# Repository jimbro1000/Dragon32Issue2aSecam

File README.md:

# Dragon 32 Issue 2a (SECAM) Reproduction

This repository contains the KiCad project files
to reproduce the SECAM variation of the Dragon 32
Issue 2a main board.

This design requires the SECAM power board to operate
correctly and will not work with the standard board.
See https://github.com/jimbro1000/Dragon32PowerSecam

## Notes

The board incorporates some factory bodges to simplify
assembly efforts.

A front and back ground plane fill has also been added
along with effort to make sure that a ground plane is 
present across most of the board.

## Video Circuit Changes

Compared to the original Dragon 32 (in PAL or NTSC form)
the SECAM version of the design requires a significant 
level of additional work to generate a viable composite
signal.

The most significant change is that the board does not 
make use of a modulator chip (the LM1889N is used on
the PAL version). Instead the generation of the FM based
composite signal is generated through discrete components.

The board is effectively split into two areas. The regular
PAL design (with a few small tweaks) and the SECAM composite
generation - located in the north section of the PCB.

## Power Board Changes

While the same 9 wire interconnect is present on both
designs, the SECAM version repurposes the 5 non-voltage
connections making the power board incompatible with the
PAL/NTSC main board and the SECAM main board incompatible
with the PAL/NTSC power board.

The original pin out provided ground, composite, audio, 5v
and a bias voltage.

The SECAM board uses the same pins as audio, composite,
luma, phiA and phiB (the last 3 forming a YPrPb signal). 
By passing the raw output of the VDG to the power board
there is space to perform additional transformation into
a genuine RGB output that is sorely missing from the original.

### RGB Calculation

The transformation is performed in two stages - first to
homogenise the signal levels of the VDG output (while it 
broadly follows the YPrPb format it doesn't meet the requried
signal voltages). The second stage performs some analogue
computation to create R-Y, G-Y and B-Y components. These
then can be added to the homogenised Y signal to create
the three R, G and B signals.

An exta calculation is needed to isolate the sync signal
that appears on the G channel.

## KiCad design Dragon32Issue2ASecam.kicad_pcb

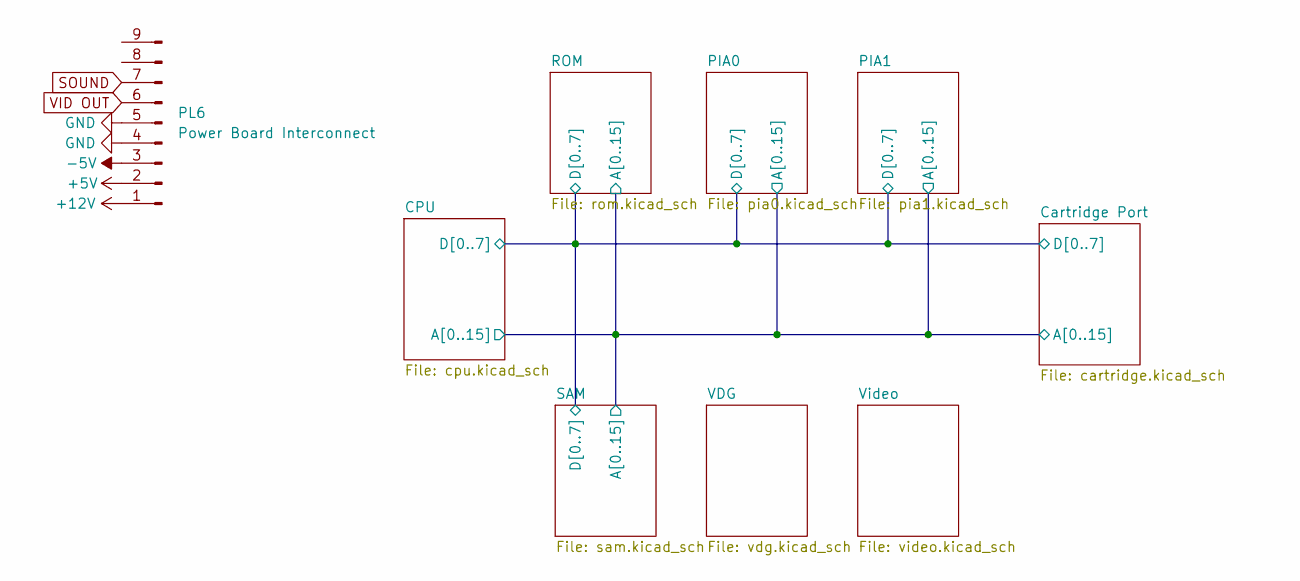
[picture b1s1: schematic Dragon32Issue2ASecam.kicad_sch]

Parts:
PL6: Power Board Interconnect; Molex_KK-396_A-41791-0009_1x09_P3.96mm_Vertical; DigiKey 2057-LHD-09-TS-ND

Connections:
+5V: PL6.2; also elsewhere on the board
+12V: PL6.1; also elsewhere on the board
-5V: PL6.3
GND: PL6.4, PL6.5; also elsewhere on the board
SOUND: PL6.7; also elsewhere on the board
VID OUT: PL6.6

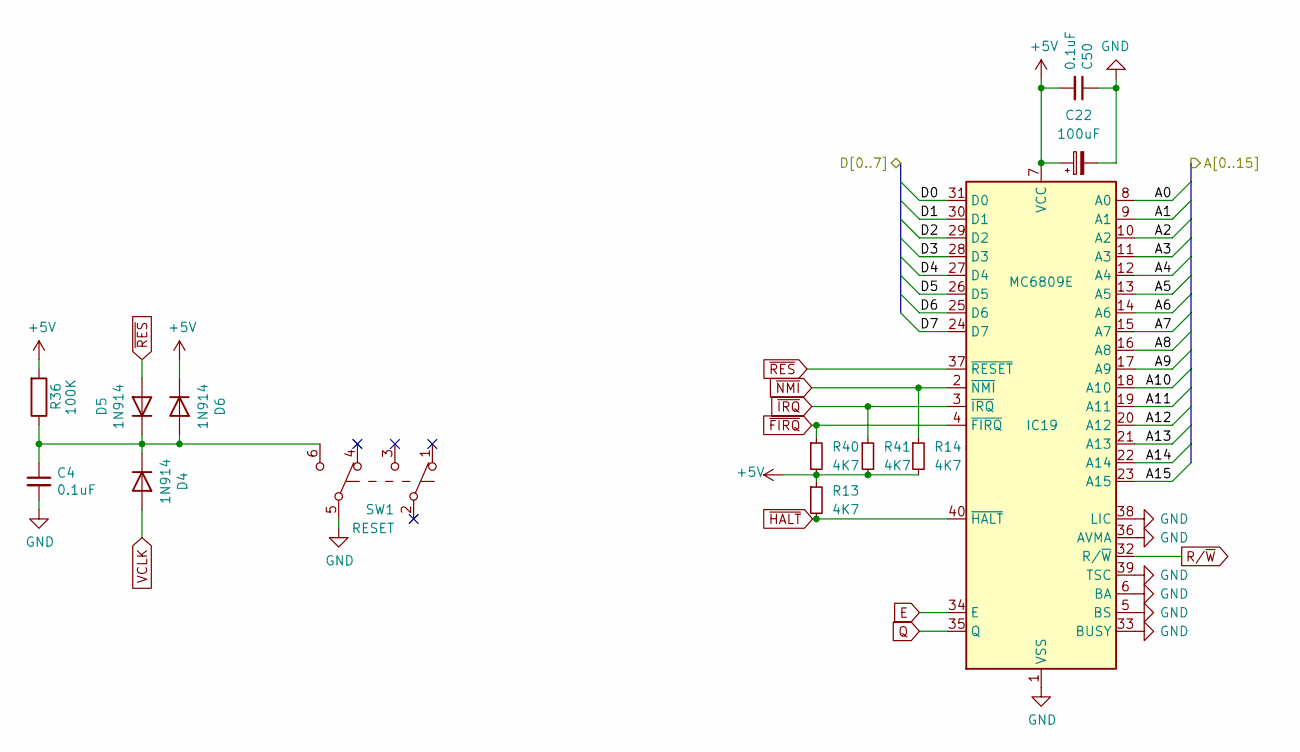
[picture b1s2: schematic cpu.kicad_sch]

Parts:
C4, C50: 0.1uF; C_Disc_D4.3mm_W1.9mm_P5.00mm; DigiKey BC1101CT-ND
C22: 100uF; CP_Radial_D8.0mm_P5.00mm; DigiKey 732-8598-1-ND
D4, D5, D6: 1N914; D_DO-35_SOD27_P12.70mm_Horizontal; DigiKey 1N914FS-ND
IC19: MC6809E; DIP-40_W15.24mm
R13, R14, R40, R41: 4K7; R_Axial_DIN0309_L9.0mm_D2.5mm_P12.70mm_Horizontal; DigiKey CF14JT4K70CT-ND
R36: 100K; R_Axial_DIN0309_L9.0mm_D2.5mm_P12.70mm_Horizontal; DigiKey CF14JT100KCT-ND
SW1: RESET; Button_AlpsAlpine_SPUN190900; DigiKey 401-1225-ND

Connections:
+5V: C22.1, C50.2, D6.1 (K), IC19.7 (VCC), R13.1, R14.2, R36.2, R40.2, R41.2; also elsewhere on the board
/CPU/A0: IC19.8 (A0); also elsewhere on the board
/CPU/A1: IC19.9 (A1); also elsewhere on the board
/CPU/A2: IC19.10 (A2); also elsewhere on the board
/CPU/A3: IC19.11 (A3); also elsewhere on the board
/CPU/A4: IC19.12 (A4); also elsewhere on the board
/CPU/A5: IC19.13 (A5); also elsewhere on the board
/CPU/A6: IC19.14 (A6); also elsewhere on the board
/CPU/A7: IC19.15 (A7); also elsewhere on the board
/CPU/A8: IC19.16 (A8); also elsewhere on the board
/CPU/A9: IC19.17 (A9); also elsewhere on the board
/CPU/A10: IC19.18 (A10); also elsewhere on the board
/CPU/A11: IC19.19 (A11); also elsewhere on the board
/CPU/A12: IC19.20 (A12); also elsewhere on the board
/CPU/A13: IC19.21 (A13); also elsewhere on the board
/CPU/A14: IC19.22 (A14); also elsewhere on the board
/CPU/A15: IC19.23 (A15); also elsewhere on the board
/CPU/D0: IC19.31 (D0); also elsewhere on the board
/CPU/D1: IC19.30 (D1); also elsewhere on the board
/CPU/D2: IC19.29 (D2); also elsewhere on the board
/CPU/D3: IC19.28 (D3); also elsewhere on the board
/CPU/D4: IC19.27 (D4); also elsewhere on the board
/CPU/D5: IC19.26 (D5); also elsewhere on the board
/CPU/D6: IC19.25 (D6); also elsewhere on the board
/CPU/D7: IC19.24 (D7); also elsewhere on the board
E: IC19.34 (E); also elsewhere on the board
GND: C4.2, C22.2, C50.1, IC19.1 (VSS), IC19.5 (BS), IC19.6 (BA), IC19.33 (BUSY), IC19.36 (AVMA), IC19.38 (LIC), IC19.39 (TSC), SW1.5 (B); also elsewhere on the board
unnamed: C4.1, D4.1 (K), D5.1 (K), D6.2 (A), R36.1, SW1.6 (C)
Q: IC19.35 (Q); also elsewhere on the board
R/~W: IC19.32 (R/~W); also elsewhere on the board
VCLK: D4.2 (A); also elsewhere on the board
~FIRQ: IC19.4 (~FIRQ), R40.1; also elsewhere on the board
~HALT: IC19.40 (~HALT), R13.2; also elsewhere on the board
~IRQ: IC19.3 (~IRQ), R41.1; also elsewhere on the board
~NMI: IC19.2 (~NMI), R14.1; also elsewhere on the board
~RES: D5.2 (A), IC19.37 (~RESET); also elsewhere on the board

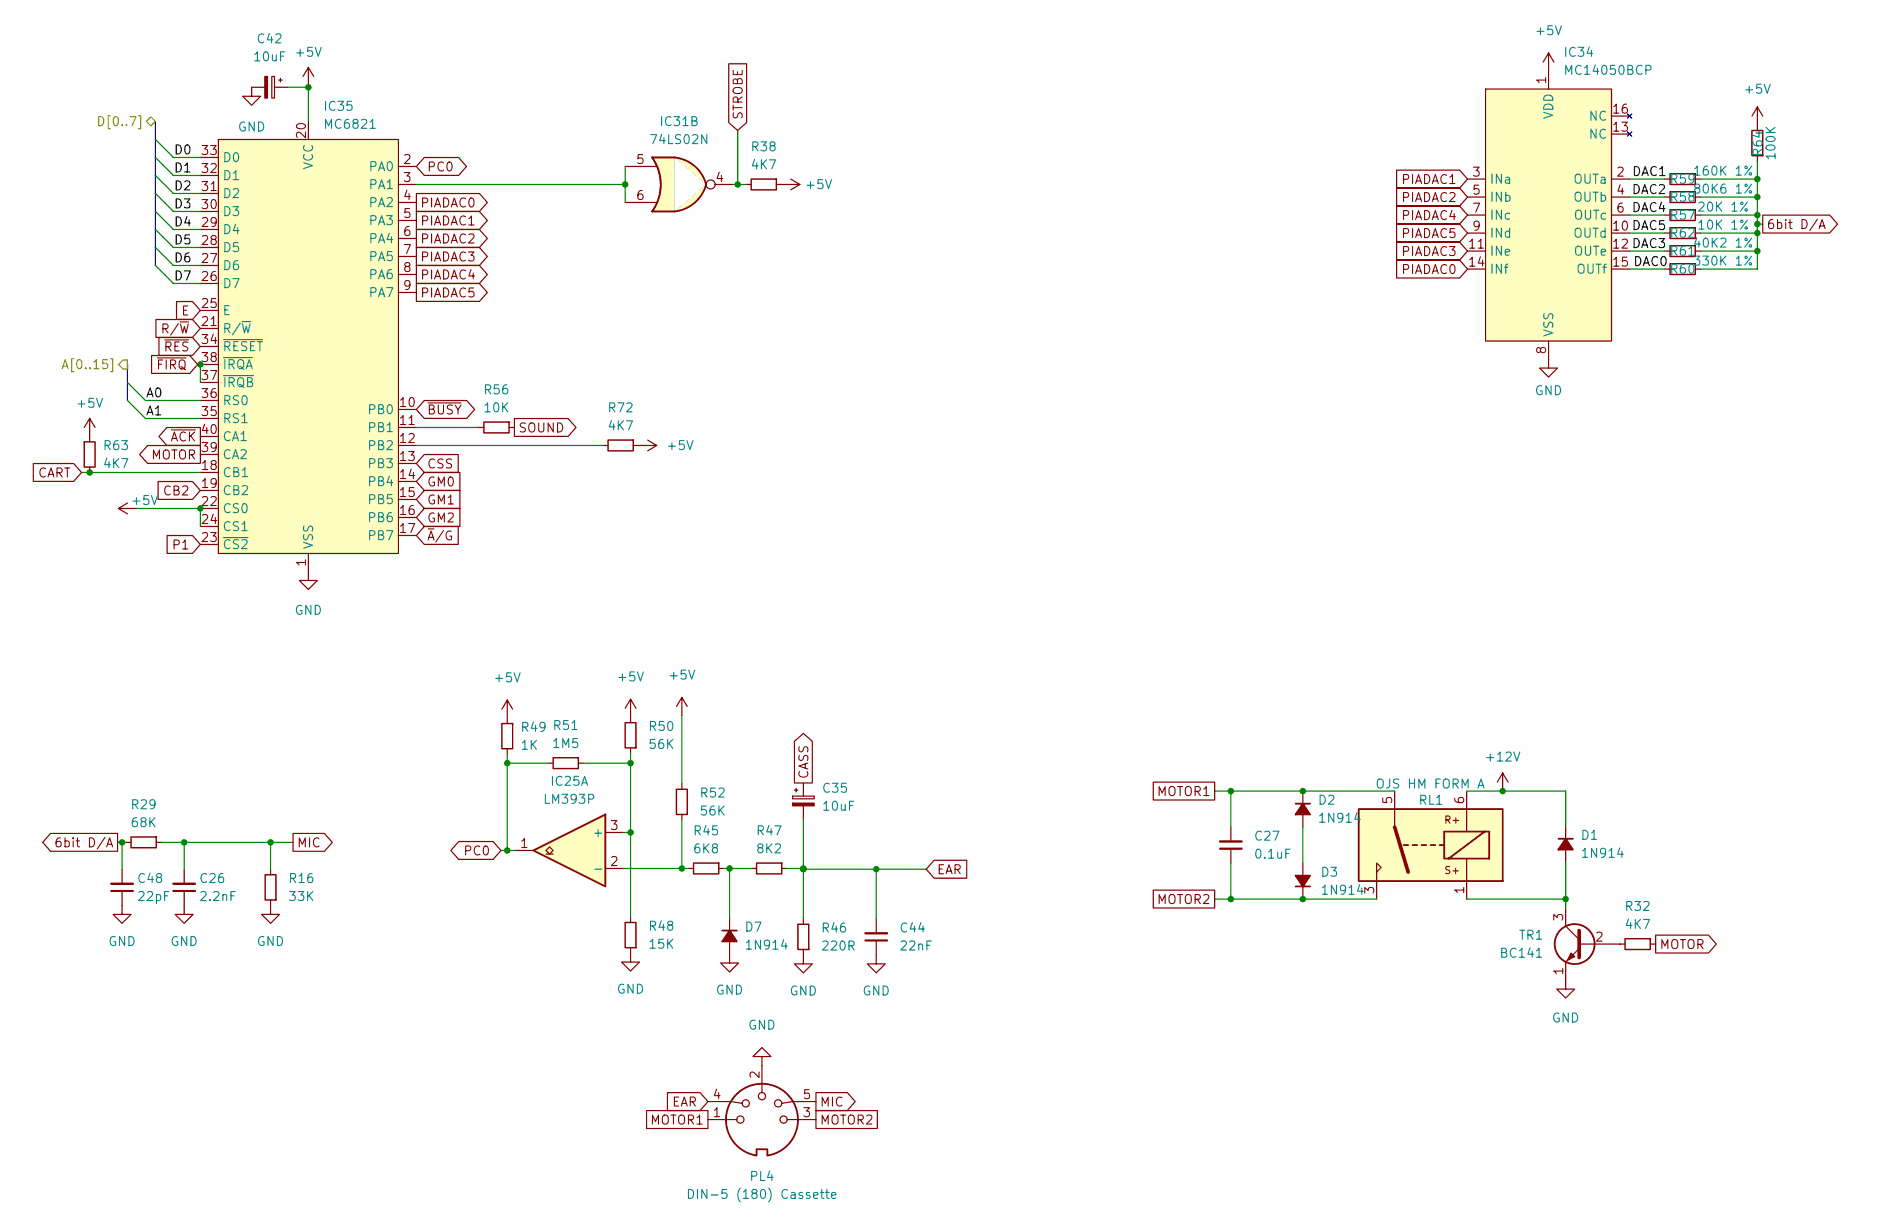
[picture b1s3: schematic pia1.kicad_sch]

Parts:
C26: 2.2nF; C_Disc_D4.3mm_W1.9mm_P5.00mm; DigiKey BC1074CT-ND
C27: 0.1uF; C_Disc_D4.3mm_W1.9mm_P5.00mm; DigiKey BC1101CT-ND
C35, C42: 10uF; CP_Radial_D5.0mm_P2.50mm; DigiKey 732-8593-1-ND
C44: 22nF; C_Disc_D5.0mm_W2.5mm_P5.00mm; DigiKey BC2677CT-ND
C48: 22pF; C_Disc_D3.0mm_W2.0mm_P2.50mm; DigiKey 399-13930-1-ND
D1, D2, D3, D7: 1N914; D_DO-35_SOD27_P12.70mm_Horizontal; DigiKey 1N914FS-ND
IC25: LM393P; DIP-8_W7.62mm; DigiKey 296-1398-5-ND
IC31: 74LS02N; DIP-14_W7.62mm; DigiKey 296-1627-5-ND
IC34: MC14050BCP; DIP-16_W7.62mm; DigiKey 296-2056-ND
IC35: MC6821; DIP-40_W15.24mm; DigiKey 2156-MC6821CS-2156-ND
PL4: DIN-5 (180) Cassette; DIN-5_DELTRON_671-0501_45deg_Horizontal
R16: 33K; R_Axial_DIN0309_L9.0mm_D2.5mm_P12.70mm_Horizontal; DigiKey CF14JT33K0CT-ND
R29: 68K; R_Axial_DIN0309_L9.0mm_D2.5mm_P12.70mm_Horizontal; DigiKey CF14JT68K0CT-ND
R32, R38, R63: 4K7; R_Axial_DIN0309_L9.0mm_D2.5mm_P12.70mm_Horizontal; DigiKey CF14JT4K70CT-ND
R45: 6K8; R_Axial_DIN0309_L9.0mm_D2.5mm_P12.70mm_Horizontal; DigiKey CF14JT6K80CT-ND
R46: 220R; R_Axial_DIN0309_L9.0mm_D2.5mm_P12.70mm_Horizontal; DigiKey CF14JT220RCT-ND
R47: 8K2; R_Axial_DIN0309_L9.0mm_D2.5mm_P12.70mm_Horizontal; DigiKey CF14JT8K20CT-ND
R48: 15K; R_Axial_DIN0309_L9.0mm_D2.5mm_P12.70mm_Horizontal; DigiKey CF14JT15K0CT-ND
R49: 1K; R_Axial_DIN0309_L9.0mm_D2.5mm_P12.70mm_Horizontal; DigiKey CF14JT1K00CT-ND
R50, R52: 56K; R_Axial_DIN0309_L9.0mm_D2.5mm_P12.70mm_Horizontal; DigiKey CF14JT56K0CT-ND
R51: 1M5; R_Axial_DIN0309_L9.0mm_D2.5mm_P12.70mm_Horizontal; DigiKey CF14JT1M50CT-ND
R56: 10K; R_Axial_DIN0309_L9.0mm_D2.5mm_P12.70mm_Horizontal; DigiKey CF14JT10K0CT-ND
R57: 20K 1%; R_Axial_DIN0309_L9.0mm_D2.5mm_P12.70mm_Horizontal; DigiKey RNF14FTD20K0CT-ND
R58: 80K6 1%; R_Axial_DIN0309_L9.0mm_D2.5mm_P12.70mm_Horizontal; DigiKey RNF14FTD80K6CT-ND
R59: 160K 1%; R_Axial_DIN0309_L9.0mm_D2.5mm_P12.70mm_Horizontal; DigiKey S160CACT-ND
R60: 330K 1%; R_Axial_DIN0309_L9.0mm_D2.5mm_P12.70mm_Horizontal; DigiKey S330KCACT-ND
R61: 40K2 1%; R_Axial_DIN0309_L9.0mm_D2.5mm_P12.70mm_Horizontal; DigiKey RNF14FTD41K2CT-ND
R62: 10K 1%; R_Axial_DIN0309_L9.0mm_D2.5mm_P12.70mm_Horizontal; DigiKey RNF14FTD10K0CT-ND
R64: 100K; R_Axial_DIN0309_L9.0mm_D2.5mm_P12.70mm_Horizontal; DigiKey CF14JT100KCT-ND
R72: 4K7; R_Axial_DIN0309_L9.0mm_D2.5mm_P12.70mm_Horizontal; DigiKey CF14JT10K0CT-ND
RL1: OJS HM FORM A; OJS HM 10A Relay; DigiKey 41-OJS-SH-105HMF,00000-ND
TR1: BC141; TO-92_Inline_Wide; DigiKey SS8050DTACT-ND

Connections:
6bit D/A: C48.2, R29.2, R57.1, R58.1, R59.1, R60.1, R61.1, R62.1, R64.1; also elsewhere on the board
+5V: C42.1, IC34.1 (VDD), IC35.20 (VCC), IC35.22 (CS0), IC35.24 (CS1), R38.1, R49.1, R50.2, R52.2, R63.1, R64.2, R72.1; also elsewhere on the board
+12V: D1.1 (K), RL1.6; also elsewhere on the board
/CPU/A0: IC35.36 (RS0); also elsewhere on the board
/CPU/A1: IC35.35 (RS1); also elsewhere on the board
/CPU/D0: IC35.33 (D0); also elsewhere on the board
/CPU/D1: IC35.32 (D1); also elsewhere on the board
/CPU/D2: IC35.31 (D2); also elsewhere on the board
/CPU/D3: IC35.30 (D3); also elsewhere on the board
/CPU/D4: IC35.29 (D4); also elsewhere on the board
/CPU/D5: IC35.28 (D5); also elsewhere on the board
/CPU/D6: IC35.27 (D6); also elsewhere on the board
/CPU/D7: IC35.26 (D7); also elsewhere on the board
/PIA1/DAC0: IC34.15 (OUTf), R60.2
/PIA1/DAC1: IC34.2 (OUTa), R59.2
/PIA1/DAC2: IC34.4 (OUTb), R58.2
/PIA1/DAC3: IC34.12 (OUTe), R61.2
/PIA1/DAC4: IC34.6 (OUTc), R57.2
/PIA1/DAC5: IC34.10 (OUTd), R62.2
CART: IC35.18 (CB1), R63.2; also elsewhere on the board
CASS: C35.1; also elsewhere on the board
CB2: IC35.19 (CB2); also elsewhere on the board
CSS: IC35.13 (PB3); also elsewhere on the board
E: IC35.25 (E); also elsewhere on the board
EAR: C35.2, C44.2, PL4.4, R46.2, R47.1
GM0: IC35.14 (PB4); also elsewhere on the board
GM1: IC35.15 (PB5); also elsewhere on the board
GM2: IC35.16 (PB6); also elsewhere on the board
GND: C26.1, C42.2, C44.1, C48.1, D7.2 (A), IC34.8 (VSS), IC35.1 (VSS), PL4.2, R16.1, R46.1, R48.1, TR1.1 (E); also elsewhere on the board
MIC: C26.2, PL4.5, R16.2, R29.1
MOTOR: IC35.39 (CA2), R32.1
MOTOR1: C27.2, D2.1 (K), PL4.1, RL1.5
MOTOR2: C27.1, D3.1 (K), PL4.3, RL1.3
unnamed: D1.2 (A), RL1.1, TR1.3 (C)
unnamed: D2.2 (A), D3.2 (A)
unnamed: D7.1 (K), R45.1, R47.2
unnamed: IC25.3 (+), R48.2, R50.1, R51.1
unnamed: IC25.2 (-), R45.2, R52.1
unnamed: IC31.5, IC31.6, IC35.3 (PA1)
unnamed: IC35.11 (PB1), R56.2
unnamed: IC35.12 (PB2), R72.2
unnamed: R32.2, TR1.2 (B)
P1: IC35.23 (~CS2); also elsewhere on the board
PC0: IC25.1, IC35.2 (PA0), R49.2, R51.2
PIADAC0: IC34.14 (INf), IC35.4 (PA2)
PIADAC1: IC34.3 (INa), IC35.5 (PA3)
PIADAC2: IC34.5 (INb), IC35.6 (PA4)
PIADAC3: IC34.11 (INe), IC35.7 (PA5)
PIADAC4: IC34.7 (INc), IC35.8 (PA6)
PIADAC5: IC34.9 (INd), IC35.9 (PA7)
R/~W: IC35.21 (R/~W); also elsewhere on the board
SOUND: R56.1; also elsewhere on the board
STROBE: IC31.4, R38.2; also elsewhere on the board
~ACK: IC35.40 (CA1); also elsewhere on the board
~A/G: IC35.17 (PB7); also elsewhere on the board
~BUSY: IC35.10 (PB0); also elsewhere on the board
~FIRQ: IC35.37 (~IRQB), IC35.38 (~IRQA); also elsewhere on the board
~RES: IC35.34 (~RESET); also elsewhere on the board

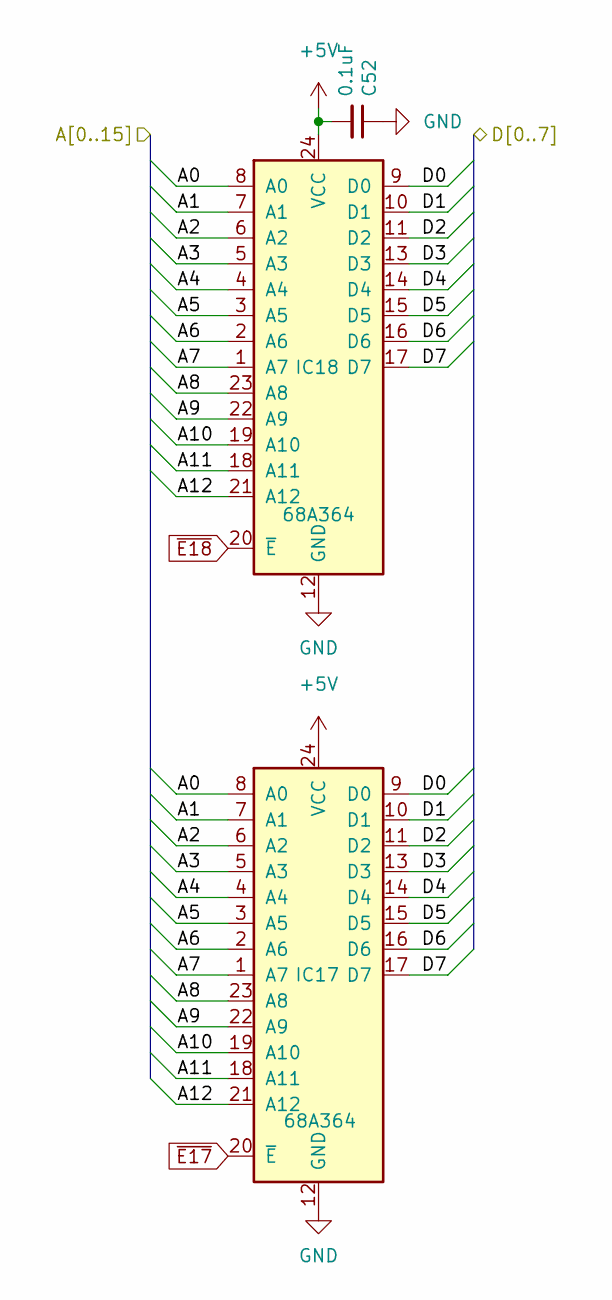
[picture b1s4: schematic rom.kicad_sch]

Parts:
C52: 0.1uF; C_Disc_D4.3mm_W1.9mm_P5.00mm; DigiKey BC1101CT-ND
IC17, IC18: 68A364; DIP-24_W15.24mm

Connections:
+5V: C52.2, IC17.24 (VCC), IC18.24 (VCC); also elsewhere on the board
/CPU/A0: IC17.8 (A0), IC18.8 (A0); also elsewhere on the board
/CPU/A1: IC17.7 (A1), IC18.7 (A1); also elsewhere on the board
/CPU/A2: IC17.6 (A2), IC18.6 (A2); also elsewhere on the board
/CPU/A3: IC17.5 (A3), IC18.5 (A3); also elsewhere on the board
/CPU/A4: IC17.4 (A4), IC18.4 (A4); also elsewhere on the board
/CPU/A5: IC17.3 (A5), IC18.3 (A5); also elsewhere on the board
/CPU/A6: IC17.2 (A6), IC18.2 (A6); also elsewhere on the board
/CPU/A7: IC17.1 (A7), IC18.1 (A7); also elsewhere on the board
/CPU/A8: IC17.23 (A8), IC18.23 (A8); also elsewhere on the board
/CPU/A9: IC17.22 (A9), IC18.22 (A9); also elsewhere on the board
/CPU/A10: IC17.19 (A10), IC18.19 (A10); also elsewhere on the board
/CPU/A11: IC17.18 (A11), IC18.18 (A11); also elsewhere on the board
/CPU/A12: IC17.21 (A12), IC18.21 (A12); also elsewhere on the board
/CPU/D0: IC17.9 (D0), IC18.9 (D0); also elsewhere on the board
/CPU/D1: IC17.10 (D1), IC18.10 (D1); also elsewhere on the board
/CPU/D2: IC17.11 (D2), IC18.11 (D2); also elsewhere on the board
/CPU/D3: IC17.13 (D3), IC18.13 (D3); also elsewhere on the board
/CPU/D4: IC17.14 (D4), IC18.14 (D4); also elsewhere on the board
/CPU/D5: IC17.15 (D5), IC18.15 (D5); also elsewhere on the board
/CPU/D6: IC17.16 (D6), IC18.16 (D6); also elsewhere on the board
/CPU/D7: IC17.17 (D7), IC18.17 (D7); also elsewhere on the board
GND: C52.1, IC17.12 (GND), IC18.12 (GND); also elsewhere on the board
~E17: IC17.20 (~E); also elsewhere on the board
~E18: IC18.20 (~E); also elsewhere on the board

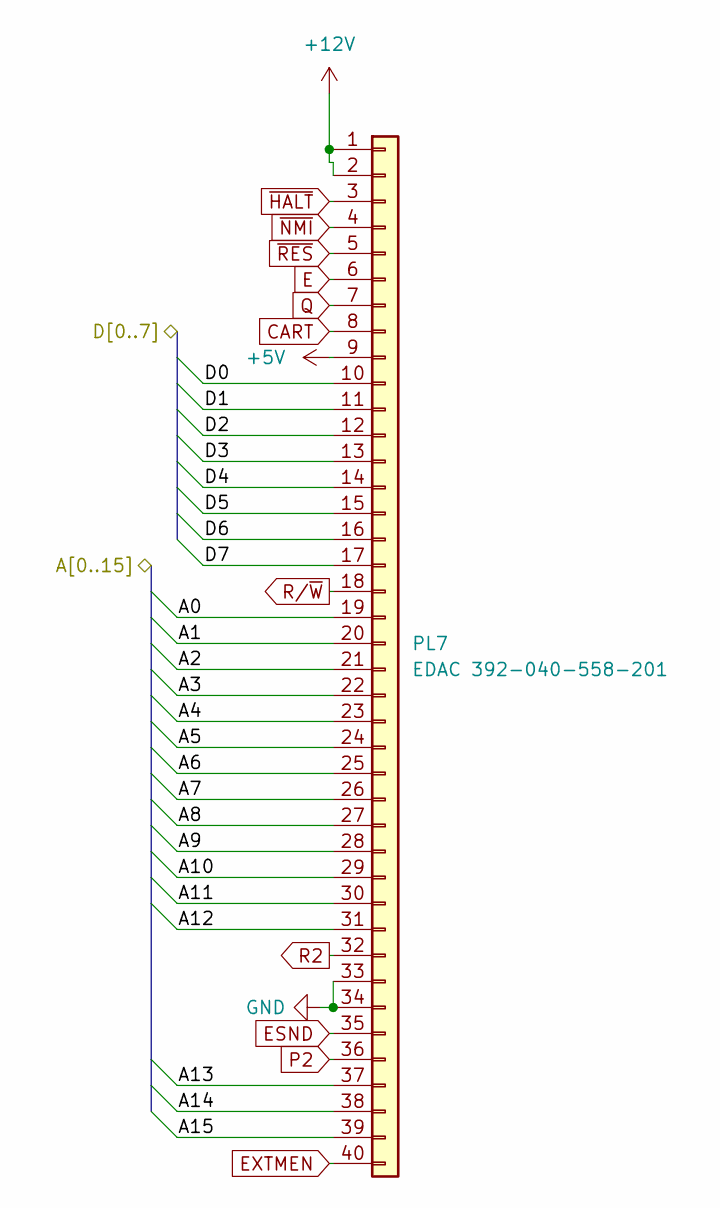
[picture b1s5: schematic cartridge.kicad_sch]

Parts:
PL7: EDAC 392-040-558-201; Edge_2x20_P2.54mm_OvalMP; DigiKey 151-395-040-558-201-ND

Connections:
+5V: PL7.9; also elsewhere on the board
+12V: PL7.1, PL7.2; also elsewhere on the board
/CPU/A0: PL7.19; also elsewhere on the board
/CPU/A1: PL7.20; also elsewhere on the board
/CPU/A2: PL7.21; also elsewhere on the board
/CPU/A3: PL7.22; also elsewhere on the board
/CPU/A4: PL7.23; also elsewhere on the board
/CPU/A5: PL7.24; also elsewhere on the board
/CPU/A6: PL7.25; also elsewhere on the board
/CPU/A7: PL7.26; also elsewhere on the board
/CPU/A8: PL7.27; also elsewhere on the board
/CPU/A9: PL7.28; also elsewhere on the board
/CPU/A10: PL7.29; also elsewhere on the board
/CPU/A11: PL7.30; also elsewhere on the board
/CPU/A12: PL7.31; also elsewhere on the board
/CPU/A13: PL7.37; also elsewhere on the board
/CPU/A14: PL7.38; also elsewhere on the board
/CPU/A15: PL7.39; also elsewhere on the board
/CPU/D0: PL7.10; also elsewhere on the board
/CPU/D1: PL7.11; also elsewhere on the board
/CPU/D2: PL7.12; also elsewhere on the board
/CPU/D3: PL7.13; also elsewhere on the board
/CPU/D4: PL7.14; also elsewhere on the board
/CPU/D5: PL7.15; also elsewhere on the board
/CPU/D6: PL7.16; also elsewhere on the board
/CPU/D7: PL7.17; also elsewhere on the board
CART: PL7.8; also elsewhere on the board
E: PL7.6; also elsewhere on the board
ESND: PL7.35; also elsewhere on the board
EXTMEN: PL7.40; also elsewhere on the board
GND: PL7.33, PL7.34; also elsewhere on the board
P2: PL7.36; also elsewhere on the board
Q: PL7.7; also elsewhere on the board
R2: PL7.32; also elsewhere on the board
R/~W: PL7.18; also elsewhere on the board
~HALT: PL7.3; also elsewhere on the board
~NMI: PL7.4; also elsewhere on the board
~RES: PL7.5; also elsewhere on the board

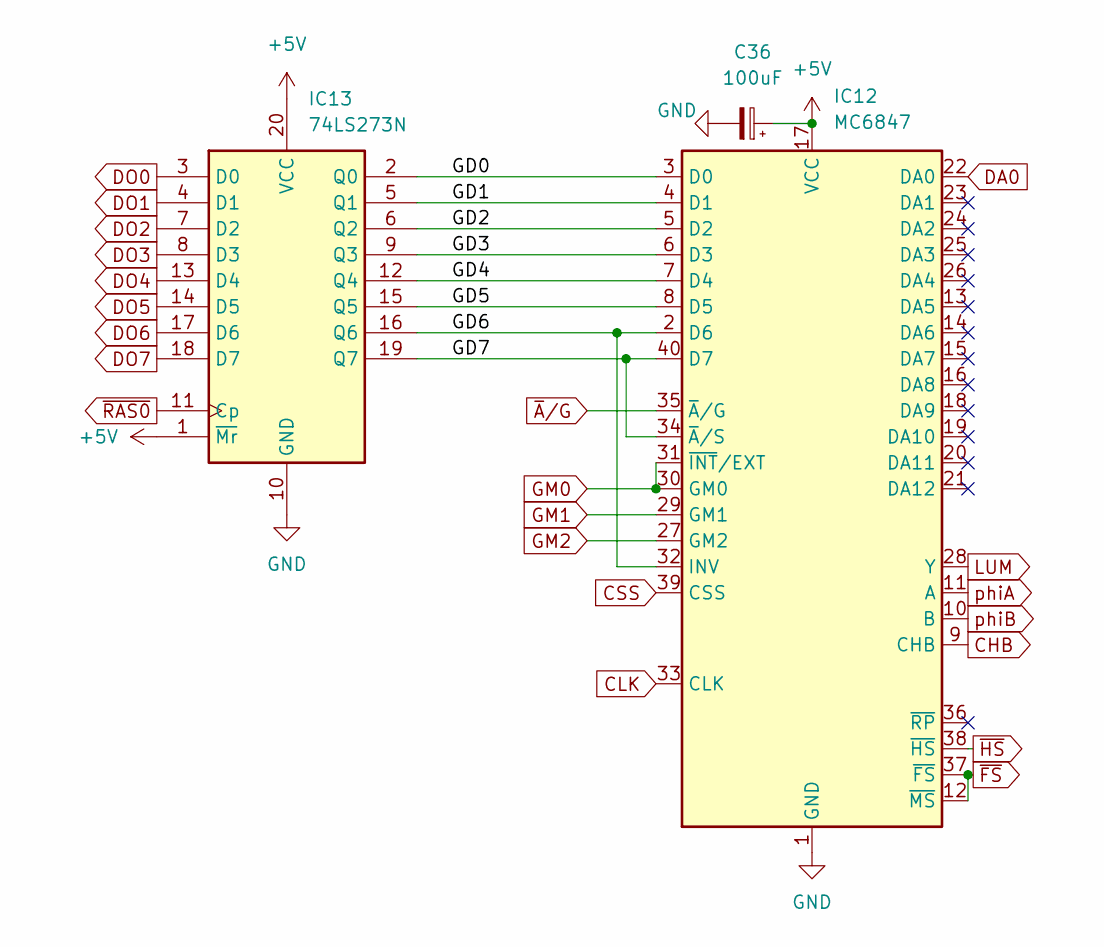
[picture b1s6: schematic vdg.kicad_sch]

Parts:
C36: 100uF; CP_Radial_D6.3mm_P2.50mm; DigiKey 732-8598-1-ND
IC12: MC6847; DIP-40_W15.24mm
IC13: 74LS273N; DIP-20_W7.62mm; DigiKey 296-1657-5-ND

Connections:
+5V: C36.1, IC12.17 (VCC), IC13.1 (~Mr), IC13.20 (VCC); also elsewhere on the board
/VDG/GD0: IC12.3 (D0), IC13.2 (Q0)
/VDG/GD1: IC12.4 (D1), IC13.5 (Q1)
/VDG/GD2: IC12.5 (D2), IC13.6 (Q2)
/VDG/GD3: IC12.6 (D3), IC13.9 (Q3)
/VDG/GD4: IC12.7 (D4), IC13.12 (Q4)
/VDG/GD5: IC12.8 (D5), IC13.15 (Q5)
/VDG/GD6: IC12.2 (D6), IC12.32 (INV), IC13.16 (Q6)
/VDG/GD7: IC12.34 (~A/S), IC12.40 (D7), IC13.19 (Q7)
CHB: IC12.9 (CHB)
CLK: IC12.33 (CLK)
CSS: IC12.39 (CSS); also elsewhere on the board
DA0: IC12.22 (DA0); also elsewhere on the board
DO0: IC13.3 (D0); also elsewhere on the board
DO1: IC13.4 (D1); also elsewhere on the board
DO2: IC13.7 (D2); also elsewhere on the board
DO3: IC13.8 (D3); also elsewhere on the board
DO4: IC13.13 (D4); also elsewhere on the board
DO5: IC13.14 (D5); also elsewhere on the board
DO6: IC13.17 (D6); also elsewhere on the board
DO7: IC13.18 (D7); also elsewhere on the board
GM0: IC12.30 (GM0), IC12.31 (~INT/EXT); also elsewhere on the board
GM1: IC12.29 (GM1); also elsewhere on the board
GM2: IC12.27 (GM2); also elsewhere on the board
GND: C36.2, IC12.1 (GND), IC13.10 (GND); also elsewhere on the board
LUM: IC12.28 (Y)
phiA: IC12.11 (A)
phiB: IC12.10 (B)
~A/G: IC12.35 (~A/G); also elsewhere on the board
~FS: IC12.12 (~MS), IC12.37 (~FS); also elsewhere on the board
~HS: IC12.38 (~HS)
~RAS0: IC13.11 (Cp); also elsewhere on the board

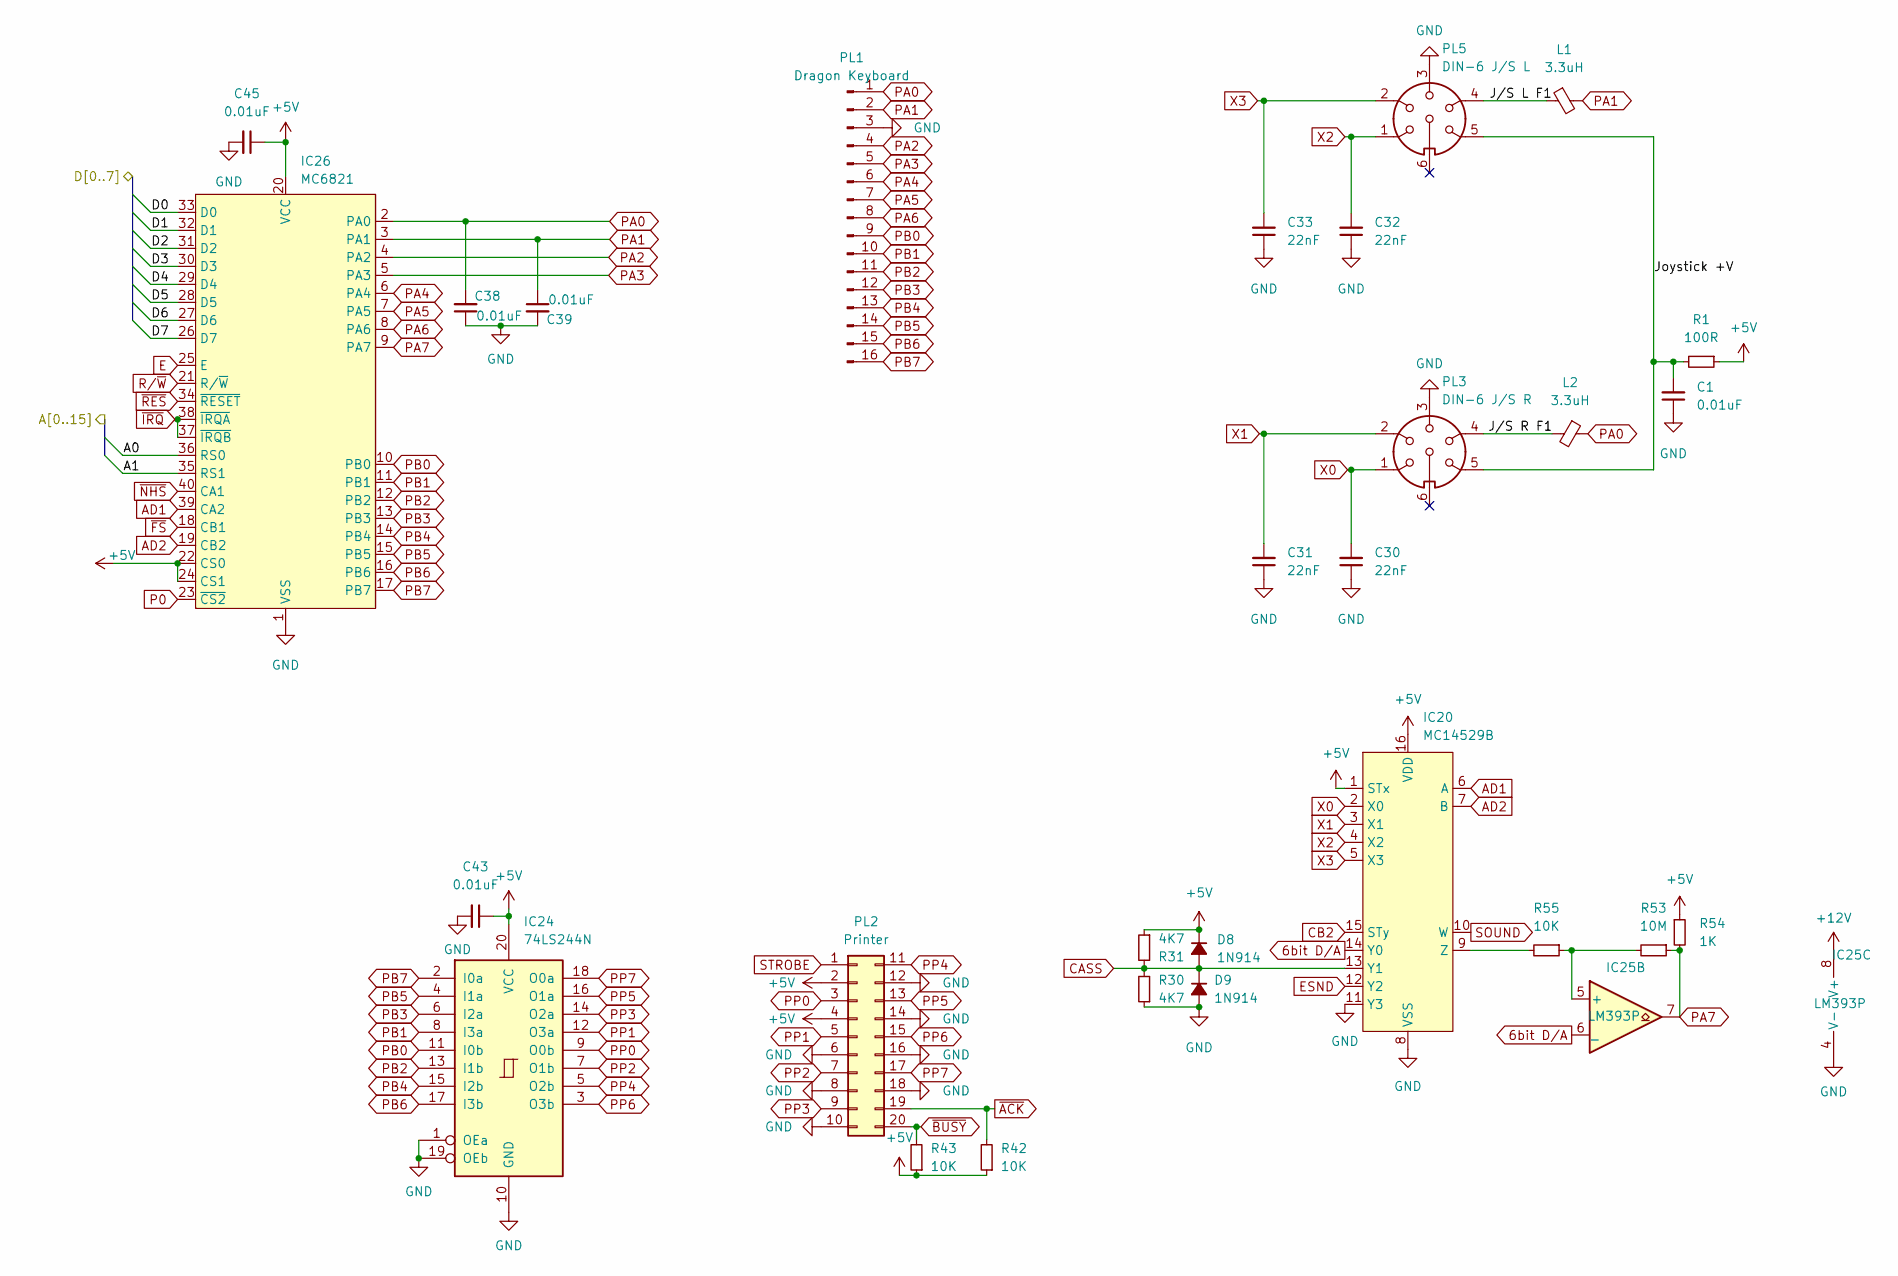
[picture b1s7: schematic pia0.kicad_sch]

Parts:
C1, C43, C45: 0.01uF; C_Disc_D4.3mm_W1.9mm_P5.00mm; DigiKey BC2662CT-ND
C30, C31, C32, C33: 22nF; C_Disc_D5.0mm_W2.5mm_P5.00mm; DigiKey BC2677CT-ND
C38, C39: 0.01uF; C_Disc_D4.3mm_W1.9mm_P5.00mm; DigiKey BC1101CT-ND
D8, D9: 1N914; D_DO-35_SOD27_P12.70mm_Horizontal; DigiKey 1N914FS-ND
IC20: MC14529B; DIP-16_W7.62mm; DigiKey CD4529BCN-ND
IC24: 74LS244N; DIP-20_W7.62mm; DigiKey 296-1653-5-ND
IC25: LM393P; DIP-8_W7.62mm; DigiKey 296-1398-5-ND
IC26: MC6821; DIP-40_W15.24mm; DigiKey 2156-MC6821CS-2156-ND
L1, L2: 3.3uH; L_Axial_L7.0mm_D3.3mm_P12.70mm_Horizontal_Fastron_MICC; DigiKey 495-5561-1-ND
PL1: Dragon Keyboard; PinHeader_1x16_P2.54mm_Vertical; DigiKey 952-2521-ND
PL2: Printer; IDC-Header_2x10-1MP_P2.54mm_Latch_Horizontal; DigiKey CHR20G-ND
PL3: DIN-6 J/S R; DIN-6_DELTRON_671-0601_Horizontal
PL5: DIN-6 J/S L; DIN-6_DELTRON_671-0601_Horizontal
R1: 100R; R_Axial_DIN0309_L9.0mm_D2.5mm_P12.70mm_Horizontal; DigiKey CF14JT100RCT-ND
R30, R31: 4K7; R_Axial_DIN0309_L9.0mm_D2.5mm_P12.70mm_Horizontal; DigiKey CF14JT4K70CT-ND
R42, R43, R55: 10K; R_Axial_DIN0309_L9.0mm_D2.5mm_P12.70mm_Horizontal; DigiKey CF14JT10K0CT-ND
R53: 10M; R_Axial_DIN0309_L9.0mm_D2.5mm_P12.70mm_Horizontal; DigiKey CF14JT10M0CT-ND
R54: 1K; R_Axial_DIN0309_L9.0mm_D2.5mm_P12.70mm_Horizontal; DigiKey CF14JT1K00CT-ND

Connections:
6bit D/A: IC20.14 (Y0), IC25.6 (_); also elsewhere on the board
+5V: C43.1, C45.1, D8.1 (K), IC20.1 (STx), IC20.16 (VDD), IC24.20 (VCC), IC26.20 (VCC), IC26.22 (CS0), IC26.24 (CS1), PL2.2, PL2.4, R1.1, R31.1, R42.1, R43.1, R54.1; also elsewhere on the board
+12V: IC25.8 (V+); also elsewhere on the board
/CPU/A0: IC26.36 (RS0); also elsewhere on the board
/CPU/A1: IC26.35 (RS1); also elsewhere on the board
/CPU/D0: IC26.33 (D0); also elsewhere on the board
/CPU/D1: IC26.32 (D1); also elsewhere on the board
/CPU/D2: IC26.31 (D2); also elsewhere on the board
/CPU/D3: IC26.30 (D3); also elsewhere on the board
/CPU/D4: IC26.29 (D4); also elsewhere on the board
/CPU/D5: IC26.28 (D5); also elsewhere on the board
/CPU/D6: IC26.27 (D6); also elsewhere on the board
/CPU/D7: IC26.26 (D7); also elsewhere on the board
/PIA0/Joystick +V: C1.2, PL3.5, PL5.5, R1.2
/PIA0/J/S L F1: L1.1, PL5.4
/PIA0/J/S R F1: L2.2, PL3.4
AD1: IC20.6 (A), IC26.39 (CA2)
AD2: IC20.7 (B), IC26.19 (CB2)
CASS: D8.2 (A), D9.1 (K), IC20.13 (Y1), R30.2, R31.2; also elsewhere on the board
CB2: IC20.15 (STy); also elsewhere on the board
E: IC26.25 (E); also elsewhere on the board
ESND: IC20.12 (Y2); also elsewhere on the board
GND: C1.1, C30.1, C31.1, C32.1, C33.1, C38.1, C39.2, C43.2, C45.2, D9.2 (A), IC20.8 (VSS), IC20.11 (Y3), IC24.1 (OEa), IC24.10 (GND), IC24.19 (OEb), IC25.4 (V-), IC26.1 (VSS), PL1.3, PL2.6, PL2.8, PL2.10, PL2.12, PL2.14, PL2.16, PL2.18, PL3.3, PL5.3, R30.1; also elsewhere on the board
unnamed: IC20.9 (Z), R55.2
unnamed: IC25.5 (+), R53.2, R55.1
P0: IC26.23 (~CS2); also elsewhere on the board
PA0: C38.2, IC26.2 (PA0), L2.1, PL1.1
PA1: C39.1, IC26.3 (PA1), L1.2, PL1.2
PA2: IC26.4 (PA2), PL1.4
PA3: IC26.5 (PA3), PL1.5
PA4: IC26.6 (PA4), PL1.6
PA5: IC26.7 (PA5), PL1.7
PA6: IC26.8 (PA6), PL1.8
PA7: IC25.7, IC26.9 (PA7), R53.1, R54.2
PB0: IC24.11 (I0b), IC26.10 (PB0), PL1.9
PB1: IC24.8 (I3a), IC26.11 (PB1), PL1.10
PB2: IC24.13 (I1b), IC26.12 (PB2), PL1.11
PB3: IC24.6 (I2a), IC26.13 (PB3), PL1.12
PB4: IC24.15 (I2b), IC26.14 (PB4), PL1.13
PB5: IC24.4 (I1a), IC26.15 (PB5), PL1.14
PB6: IC24.17 (I3b), IC26.16 (PB6), PL1.15
PB7: IC24.2 (I0a), IC26.17 (PB7), PL1.16
PP0: IC24.9 (O0b), PL2.3
PP1: IC24.12 (O3a), PL2.5
PP2: IC24.7 (O1b), PL2.7
PP3: IC24.14 (O2a), PL2.9
PP4: IC24.5 (O2b), PL2.11
PP5: IC24.16 (O1a), PL2.13
PP6: IC24.3 (O3b), PL2.15
PP7: IC24.18 (O0a), PL2.17
R/~W: IC26.21 (R/~W); also elsewhere on the board
SOUND: IC20.10 (W); also elsewhere on the board
STROBE: PL2.1; also elsewhere on the board
X0: C30.2, IC20.2 (X0), PL3.1
X1: C31.2, IC20.3 (X1), PL3.2
X2: C32.2, IC20.4 (X2), PL5.1
X3: C33.2, IC20.5 (X3), PL5.2
~ACK: PL2.19, R42.2; also elsewhere on the board
~BUSY: PL2.20, R43.2; also elsewhere on the board
~FS: IC26.18 (CB1); also elsewhere on the board
~IRQ: IC26.37 (~IRQB), IC26.38 (~IRQA); also elsewhere on the board
~NHS: IC26.40 (CA1); also elsewhere on the board
~RES: IC26.34 (~RESET); also elsewhere on the board
